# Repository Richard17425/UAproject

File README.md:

# **UAproject** (ReadOnly)
These are the projects I was responsible for when I was in University of Alberta, summer 2022. 
The projects this folder include are:

-  ## [**Cane**](Cane/scirobotics.abg6594_sm.pdf) 
-  ## [**Motion Sensor Glove**](Motion%20Sensor%20Glove/Instruction.pdf)
  
-  ## [**Prosthetic Hand**](Prosthetic%20Hand/06_01_22_abstract-presentation.pdf)

You can find details of these project in the folders.

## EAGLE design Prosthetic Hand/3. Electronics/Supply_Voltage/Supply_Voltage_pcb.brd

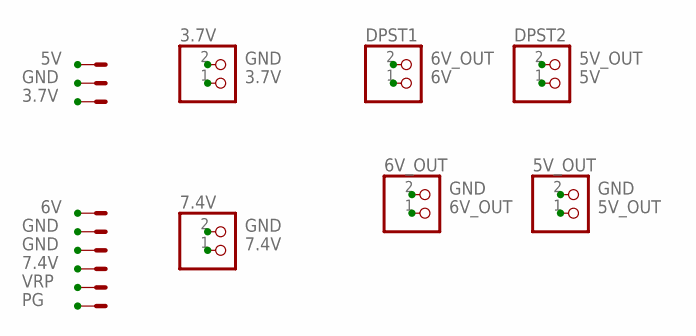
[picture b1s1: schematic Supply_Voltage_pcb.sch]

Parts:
3.7V, 5V_OUT, 6V_OUT, 7.4V: JST_2PIN-THM; JST-PH-2-THM
DPST1, DPST2: JST_2PIN-THM; JST-PH-2-THM
VC-3.7V-5V: 22-23-2031
VC-7.4V-6V: 22-23-2061

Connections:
3.7V: 3.7V.1 (2), VC-3.7V-5V.3
5V: DPST2.1 (2), VC-3.7V-5V.1
5V_OUT: 5V_OUT.1 (2), DPST2.2 (1)
6V: DPST1.1 (2), VC-7.4V-6V.1
6V_OUT: 6V_OUT.1 (2), DPST1.2 (1)
7.4V: 7.4V.1 (2), VC-7.4V-6V.4
GND: 3.7V.2 (1), 5V_OUT.2 (1), 6V_OUT.2 (1), 7.4V.2 (1), VC-3.7V-5V.2, VC-7.4V-6V.2, VC-7.4V-6V.3
PG: VC-7.4V-6V.6
VRP: VC-7.4V-6V.5

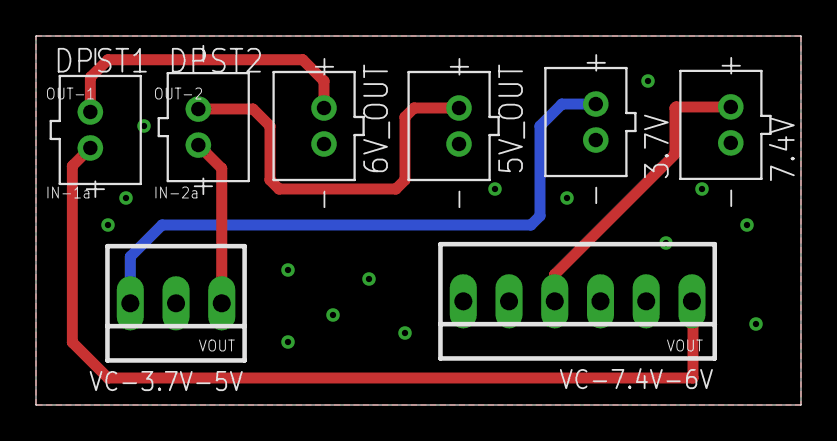
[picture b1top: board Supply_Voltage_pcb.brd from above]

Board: 2 copper layers, 42.5 x 20.5 mm, 8 parts (0 on the bottom side), 7 nets.

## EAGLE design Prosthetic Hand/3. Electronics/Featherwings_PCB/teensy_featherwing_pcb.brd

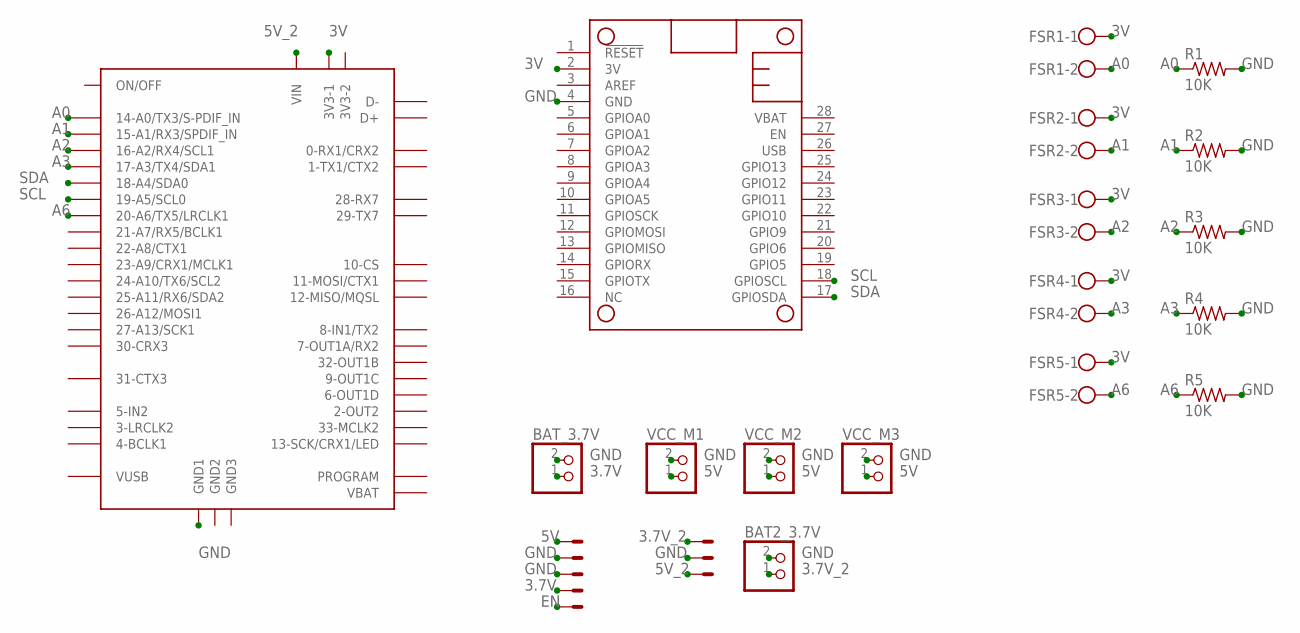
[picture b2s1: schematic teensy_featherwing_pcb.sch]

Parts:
5V_1A: 22-23-2031
5V_3A: 22-23-2051
BAT2_3.7V: JST_2PIN-THM; JST-PH-2-THM
BAT_3.7V: JST_2PIN-THM; JST-PH-2-THM
DC_MOTOR_DRIVER: FEATHERWING_NODIM; FEATHERWING_DIM
FSR1, FSR2, FSR3, FSR4, FSR5: W237-102
R1, R2, R3, R4, R5: 10K; 0207/10
U$1: TEENSY40
VCC_M1, VCC_M2, VCC_M3: JST_2PIN-THM; JST-PH-2-THM

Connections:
3.7V: 5V_3A.4, BAT_3.7V.1 (2)
3.7V_2: 5V_1A.1, BAT2_3.7V.1 (2)
3V: DC_MOTOR_DRIVER.2 (3V), FSR1.1, FSR2.1, FSR3.1, FSR4.1, FSR5.1, U$1.3V3-1
5V: 5V_3A.1, VCC_M1.1 (2), VCC_M2.1 (2), VCC_M3.1 (2)
5V_2: 5V_1A.3, U$1.VIN
A0: FSR1.2, R1.1, U$1.14-A0/TX3/S-PFI_OUT (14-A0/TX3/S-PDIF_IN)
A1: FSR2.2, R2.1, U$1.15-A1/RX3/S-PDIF_IN (15-A1/RX3/SPDIF_IN)
A2: FSR3.2, R3.1, U$1.16-A2/RX4/SCL1
A3: FSR4.2, R4.1, U$1.17-A3/TX4/SDA1
A6: FSR5.2, R5.1, U$1.20-A6/TX5/LRCLK1
EN: 5V_3A.5
GND: 5V_1A.2, 5V_3A.2, 5V_3A.3, BAT2_3.7V.2 (1), BAT_3.7V.2 (1), DC_MOTOR_DRIVER.4 (GND), R1.2, R2.2, R3.2, R4.2, R5.2, U$1.GND1, VCC_M1.2 (1), VCC_M2.2 (1), VCC_M3.2 (1)
SCL: DC_MOTOR_DRIVER.18 (GPIOSCL), U$1.19-A5/SCL0
SDA: DC_MOTOR_DRIVER.17 (GPIOSDA), U$1.18-A4/SDA0

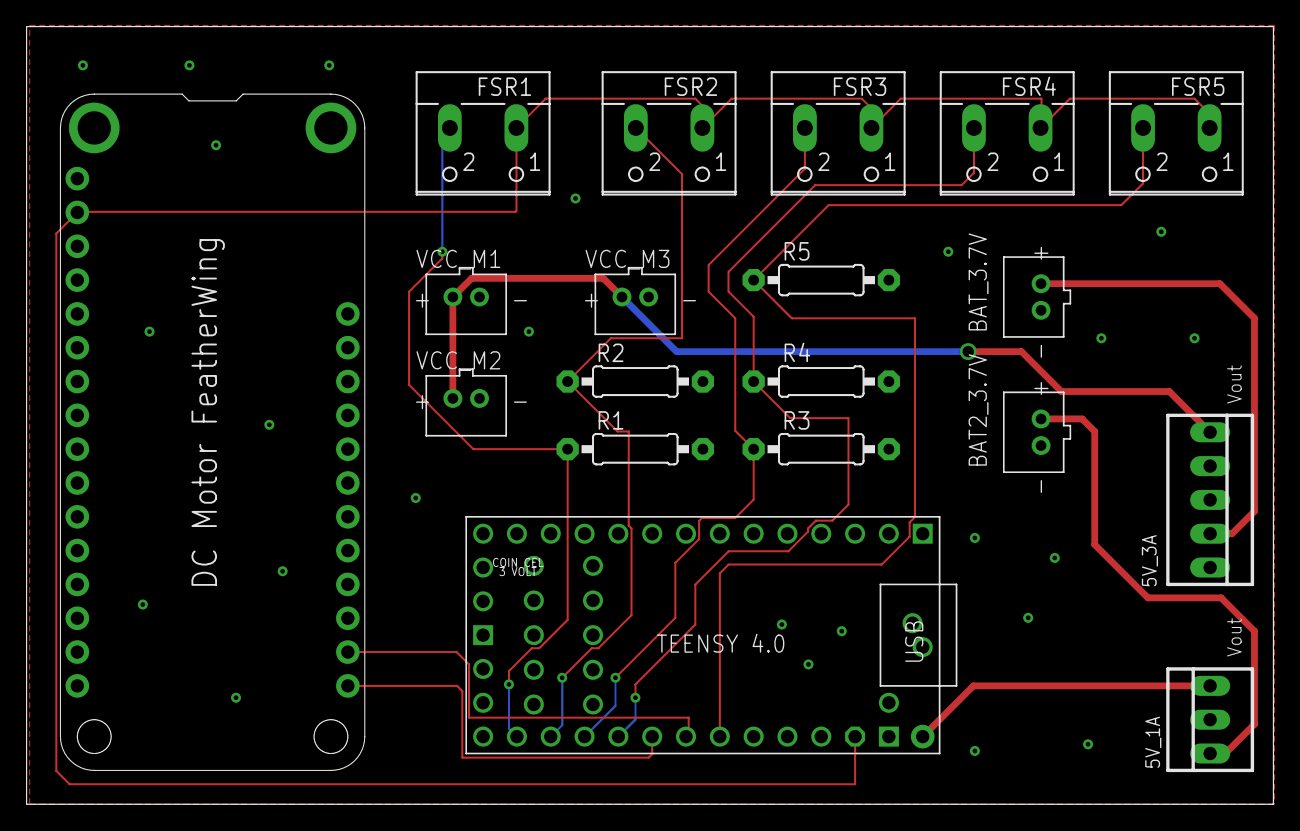
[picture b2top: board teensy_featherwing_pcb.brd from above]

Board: 2 copper layers, 93.7 x 58.4 mm, 19 parts (0 on the bottom side), 13 nets.

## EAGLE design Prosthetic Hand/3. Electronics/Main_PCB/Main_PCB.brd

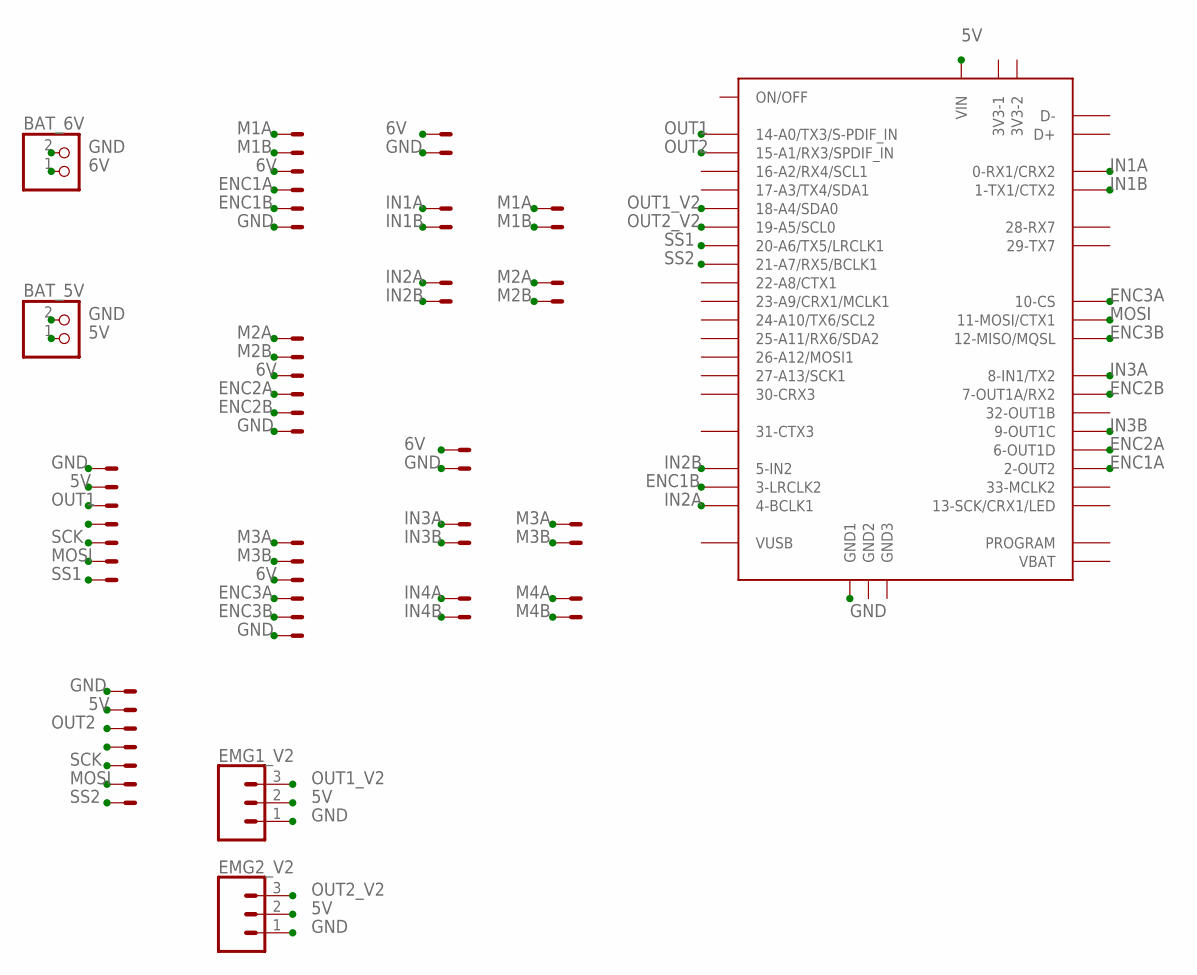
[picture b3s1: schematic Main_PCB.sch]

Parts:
BAT_5V, BAT_6V: JST_2PIN-THM; JST-PH-2-THM
EMG1, EMG2: 53047-07
EMG1_V2, EMG2_V2: CONN_03; 1X03
JST-M1, JST-M2, JST-M3: 22-23-2061
MD1-IN1, MD1-IN2, MD1-M1, MD1-M2, MD1-PWR, MD2-IN3, MD2-IN4, MD2-M3, MD2-M4, MD2-PWR: 22-23-2021
U$1: TEENSY40

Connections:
5V: BAT_5V.1 (2), EMG1.2, EMG1_V2.2, EMG2.2, EMG2_V2.2, U$1.VIN
6V: BAT_6V.1 (2), JST-M1.3, JST-M2.3, JST-M3.3, MD1-PWR.1, MD2-PWR.1
ENC1A: JST-M1.4, U$1.2-OUT2
ENC1B: JST-M1.5, U$1.3-LRCLK2
ENC2A: JST-M2.4, U$1.6-OUT1D
ENC2B: JST-M2.5, U$1.7-RX2/OUT1A (7-OUT1A/RX2)
ENC3A: JST-M3.4, U$1.10-CS/MQSR (10-CS)
ENC3B: JST-M3.5, U$1.12-MIO/MQSL (12-MISO/MQSL)
GND: BAT_5V.2 (1), BAT_6V.2 (1), EMG1.1, EMG1_V2.1, EMG2.1, EMG2_V2.1, JST-M1.6, JST-M2.6, JST-M3.6, MD1-PWR.2, MD2-PWR.2, U$1.GND1
IN1A: MD1-IN1.1, U$1.0-RX1 (0-RX1/CRX2)
IN1B: MD1-IN1.2, U$1.1-TX1 (1-TX1/CTX2)
IN2A: MD1-IN2.1, U$1.4-BCLK2 (4-BCLK1)
IN2B: MD1-IN2.2, U$1.5-IN2
IN3A: MD2-IN3.1, U$1.8-TX2/IN1 (8-IN1/TX2)
IN3B: MD2-IN3.2, U$1.9-OUT1C
IN4A: MD2-IN4.1
IN4B: MD2-IN4.2
M1A: JST-M1.1, MD1-M1.1
M1B: JST-M1.2, MD1-M1.2
M2A: JST-M2.1, MD1-M2.1
M2B: JST-M2.2, MD1-M2.2
M3A: JST-M3.1, MD2-M3.1
M3B: JST-M3.2, MD2-M3.2
M4A: MD2-M4.1
M4B: MD2-M4.2
MOSI: EMG1.6, EMG2.6, U$1.11-MOSI/CTX1
OUT1: EMG1.3, U$1.14-A0/TX3/S-PFI_OUT (14-A0/TX3/S-PDIF_IN)
OUT1_V2: EMG1_V2.3, U$1.18-A4/SDA0
OUT2: EMG2.3, U$1.15-A1/RX3/S-PDIF_IN (15-A1/RX3/SPDIF_IN)
OUT2_V2: EMG2_V2.3, U$1.19-A5/SCL0
SCK: EMG1.5, EMG2.5
SS1: EMG1.7, U$1.20-A6/TX5/LRCLK1
SS2: EMG2.7, U$1.21-A7/RX5/BCLK1

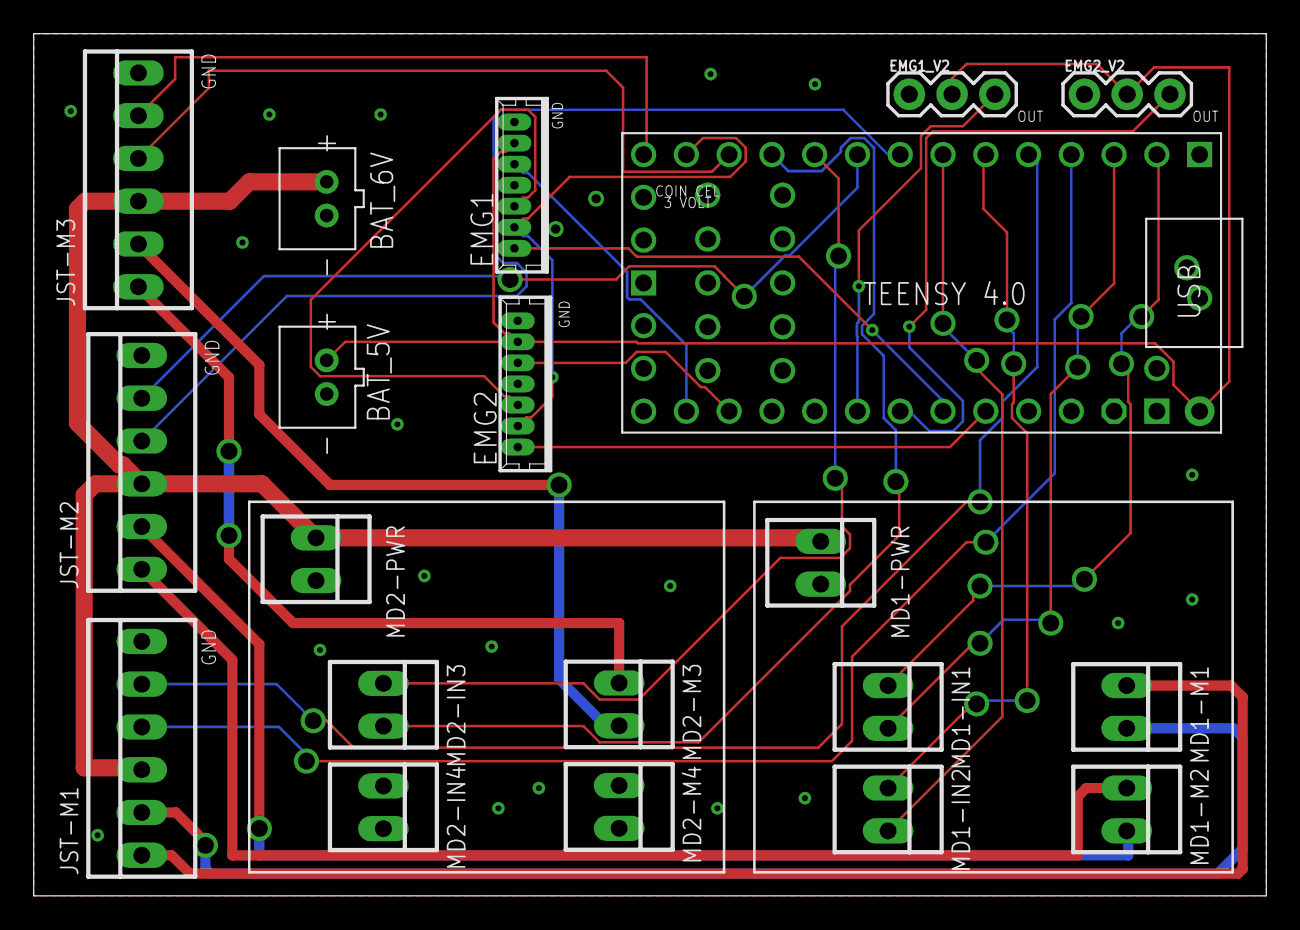
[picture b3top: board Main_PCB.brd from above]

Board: 2 copper layers, 73.2 x 51.2 mm, 20 parts (0 on the bottom side), 29 nets.

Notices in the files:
parts and their libraries:
SparkFun-Connectors: Licensing: Creative Commons ShareAlike 4.0 International - https://creativecommons.org/licenses/by-sa/4.0
